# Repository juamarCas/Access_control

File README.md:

# Access Control
This project consist on a access control system. It uses microcontroller ESP8266 for internet connection, MQTT as my data transfer protocol, NodeJS as the backend programming Language, Express as the framework for the API and MySQL as the Database.</br>

The architecture of the complete project looks like this: </br>

# Dockerizing
be executed with containers, for this, there is the _docker-compose.yml_ file, just copy the content of app.env.example and paste it in a new file called app.env same to the db.env.example and broker.env.example, then fill the data needed in both files, build the two Dockerfile that are in DataBase and webApp and then run the docker-compose.</br>
In the docker-compose file describes that the image used for the app is nodeapp, so be sure when the image is builded is named as that, or change its name as your needs, same for the image of the database.

# Directory
In this section I discribe briefly what is each folder.</br>

## Access_Control
In this folder is the microcontroller project and schematics, is programmed using the PIO IDE.</br>

## DataBase
Thise folder contains the sql file for creating the tables needed.</br>

## HW_Design
This folder includes the KiCad project for the circuit.</br>

## Web-client
This folder includes the frontend of the projects, hasn't started yet this part.</br>

## webApp
This folder includes the NodeJS code for the backend.</br>

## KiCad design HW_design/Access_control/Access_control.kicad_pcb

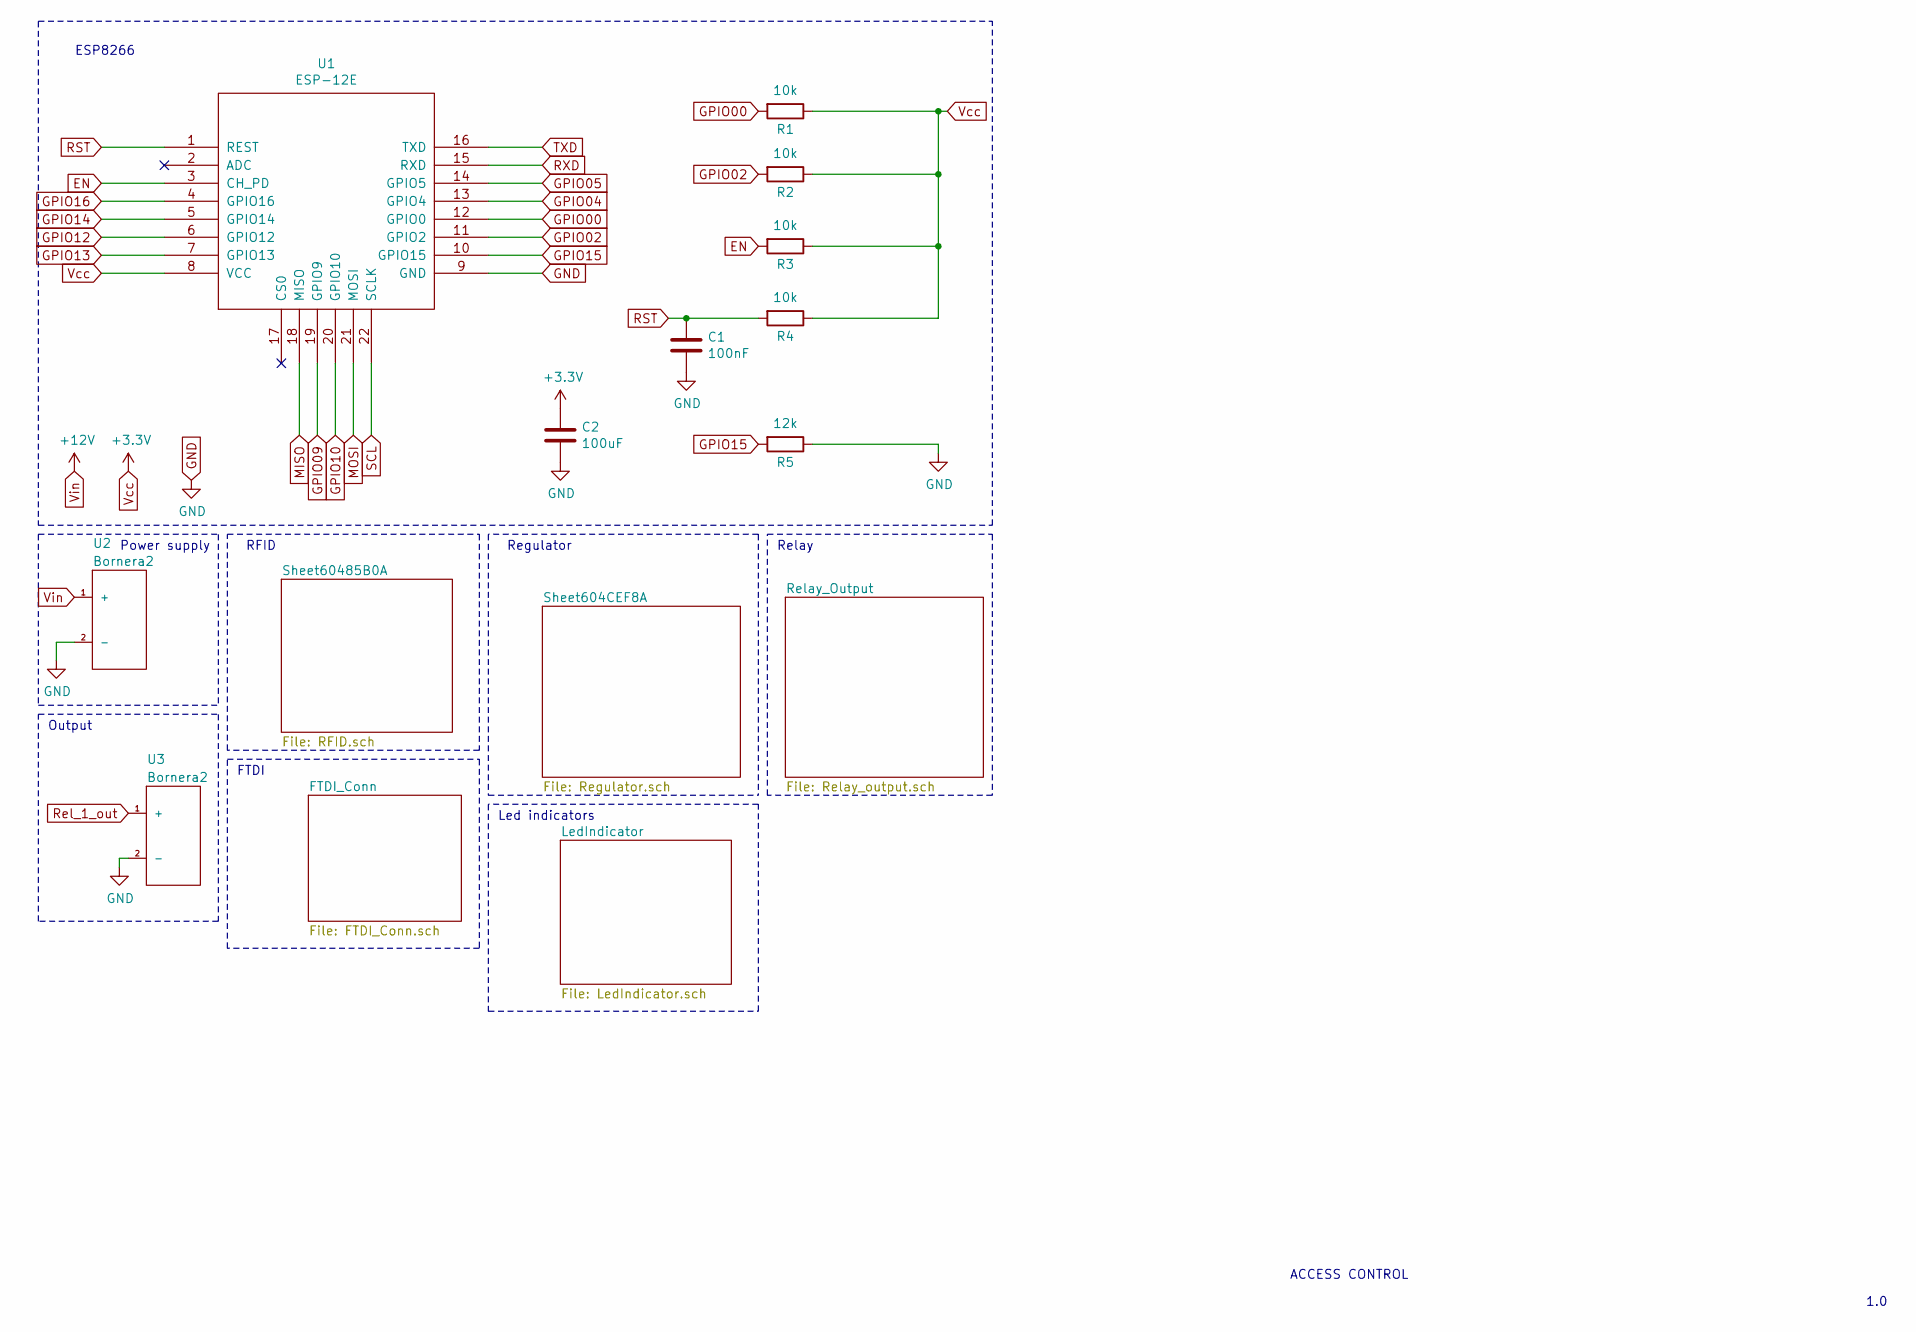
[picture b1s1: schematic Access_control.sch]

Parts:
C1: 100nF; C_1206_3216Metric
C2: 100uF; C_1206_3216Metric
R1, R2, R3, R4: 10k; R_0805_2012Metric
R5: 12k; R_0805_2012Metric
U1: ESP-12E; C_WiFiModule
U2, U3: Bornera2; Bronera_2

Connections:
EN: R3.2, U1.3 (CH_PD); also elsewhere on the board
GND: C1.2, C2.2, R5.1, U1.9 (GND), U2.2 (-), U3.2 (-); also elsewhere on the board
GPIO00: R1.2, U1.12 (GPIO0); also elsewhere on the board
GPIO02: R2.2, U1.11 (GPIO2); also elsewhere on the board
GPIO04: U1.13 (GPIO4)
GPIO05: U1.14 (GPIO5); also elsewhere on the board
GPIO09: U1.19 (GPIO9)
GPIO10: U1.20 (GPIO10)
GPIO12: U1.6 (GPIO12); also elsewhere on the board
GPIO13: U1.7 (GPIO13); also elsewhere on the board
GPIO14: U1.5 (GPIO14); also elsewhere on the board
GPIO15: R5.2, U1.10 (GPIO15); also elsewhere on the board
GPIO16: U1.4 (GPIO16); also elsewhere on the board
MISO: U1.18 (MISO)
MOSI: U1.21 (MOSI)
RST: C1.1, R4.2, U1.1 (REST)
RXD: U1.15 (RXD); also elsewhere on the board
Rel_1_out: U3.1 (+); also elsewhere on the board
SCL: U1.22 (SCLK)
TXD: U1.16 (TXD); also elsewhere on the board
Vcc: C2.1, R1.1, R2.1, R3.1, R4.1, U1.8 (VCC); also elsewhere on the board
Vin: U2.1 (+); also elsewhere on the board

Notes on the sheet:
ESP8266
RFID
Power supply
Regulator
ACCESS CONTROL
1.0
Relay
Output
FTDI
Led indicators

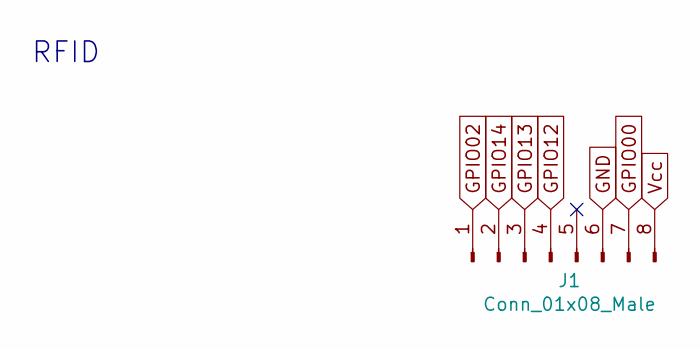
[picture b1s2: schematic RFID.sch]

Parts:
J1: Conn_01x08_Male; PinHeader_1x08_P2.54mm_Vertical

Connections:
GND: J1.6; also elsewhere on the board
GPIO00: J1.7; also elsewhere on the board
GPIO02: J1.1; also elsewhere on the board
GPIO12: J1.4; also elsewhere on the board
GPIO13: J1.3; also elsewhere on the board
GPIO14: J1.2; also elsewhere on the board
Vcc: J1.8; also elsewhere on the board

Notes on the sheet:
RFID

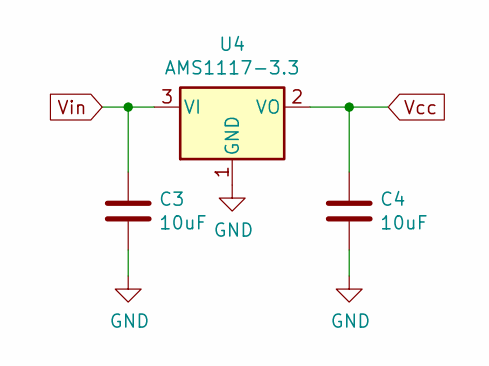
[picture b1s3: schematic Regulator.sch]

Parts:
C3, C4: 10uF; C_1206_3216Metric
U4: AMS1117-3.3; SOT-223-3_TabPin2

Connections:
GND: C3.2, C4.2, U4.1 (GND); also elsewhere on the board
Vcc: C4.1, U4.2 (VO); also elsewhere on the board
Vin: C3.1, U4.3 (VI); also elsewhere on the board

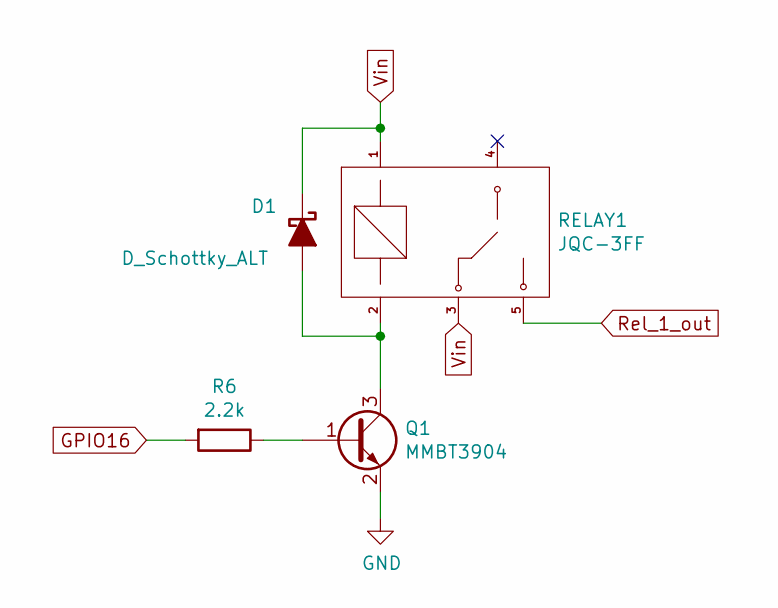
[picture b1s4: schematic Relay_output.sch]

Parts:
D1: D_Schottky_ALT; SMD_DIODE_4.6mmx2.90
Q1: MMBT3904; SOT-23
R6: 2.2k; R_0805_2012Metric
RELAY1: JQC-3FF; Relay

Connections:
GND: Q1.2 (E); also elsewhere on the board
GPIO16: R6.2; also elsewhere on the board
unnamed: D1.2 (A), Q1.3 (C), RELAY1.2
unnamed: Q1.1 (B), R6.1
Rel_1_out: RELAY1.5; also elsewhere on the board
Vin: D1.1 (K), RELAY1.1, RELAY1.3; also elsewhere on the board

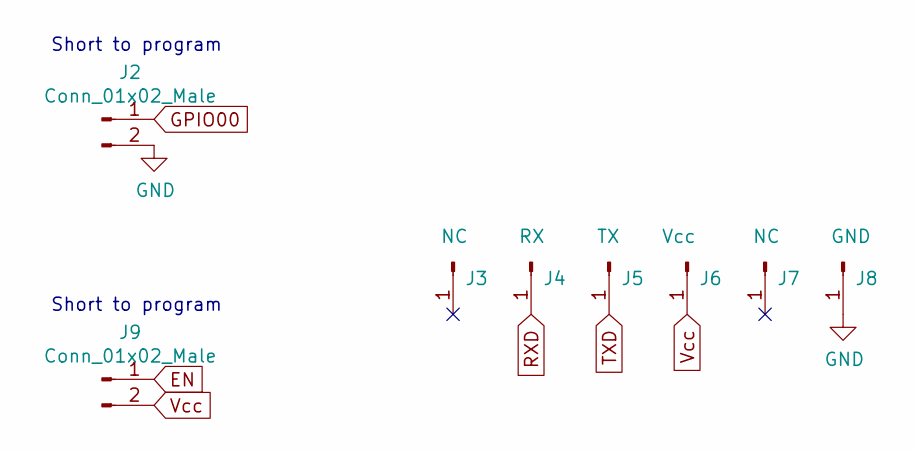
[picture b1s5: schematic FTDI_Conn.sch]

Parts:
J2, J9: Conn_01x02_Male; PinHeader_1x02_P2.54mm_Vertical
J3, J7: NC; PinHeader_1x01_P2.54mm_Vertical
J4: RX; PinHeader_1x01_P2.54mm_Vertical
J5: TX; PinHeader_1x01_P2.54mm_Vertical
J6: Vcc; PinHeader_1x01_P2.54mm_Vertical
J8: GND; PinHeader_1x01_P2.54mm_Vertical

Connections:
EN: J9.1; also elsewhere on the board
GND: J2.2, J8.1; also elsewhere on the board
GPIO00: J2.1; also elsewhere on the board
RXD: J4.1; also elsewhere on the board
TXD: J5.1; also elsewhere on the board
Vcc: J6.1, J9.2; also elsewhere on the board

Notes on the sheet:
Short to program

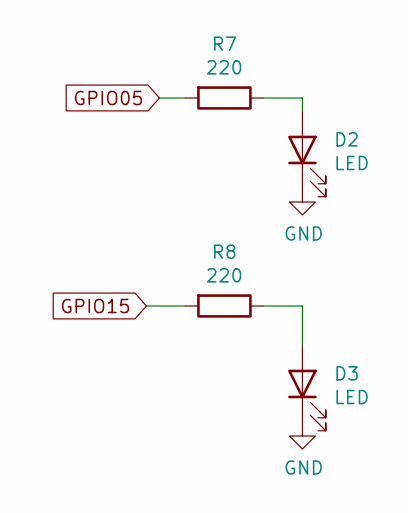
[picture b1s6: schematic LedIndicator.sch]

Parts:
D2, D3: LED; D_1206_3216Metric
R7, R8: 220; R_0805_2012Metric

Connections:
GND: D2.1 (K), D3.1 (K); also elsewhere on the board
GPIO05: R7.2; also elsewhere on the board
GPIO15: R8.2; also elsewhere on the board
unnamed: D2.2 (A), R7.1
unnamed: D3.2 (A), R8.1

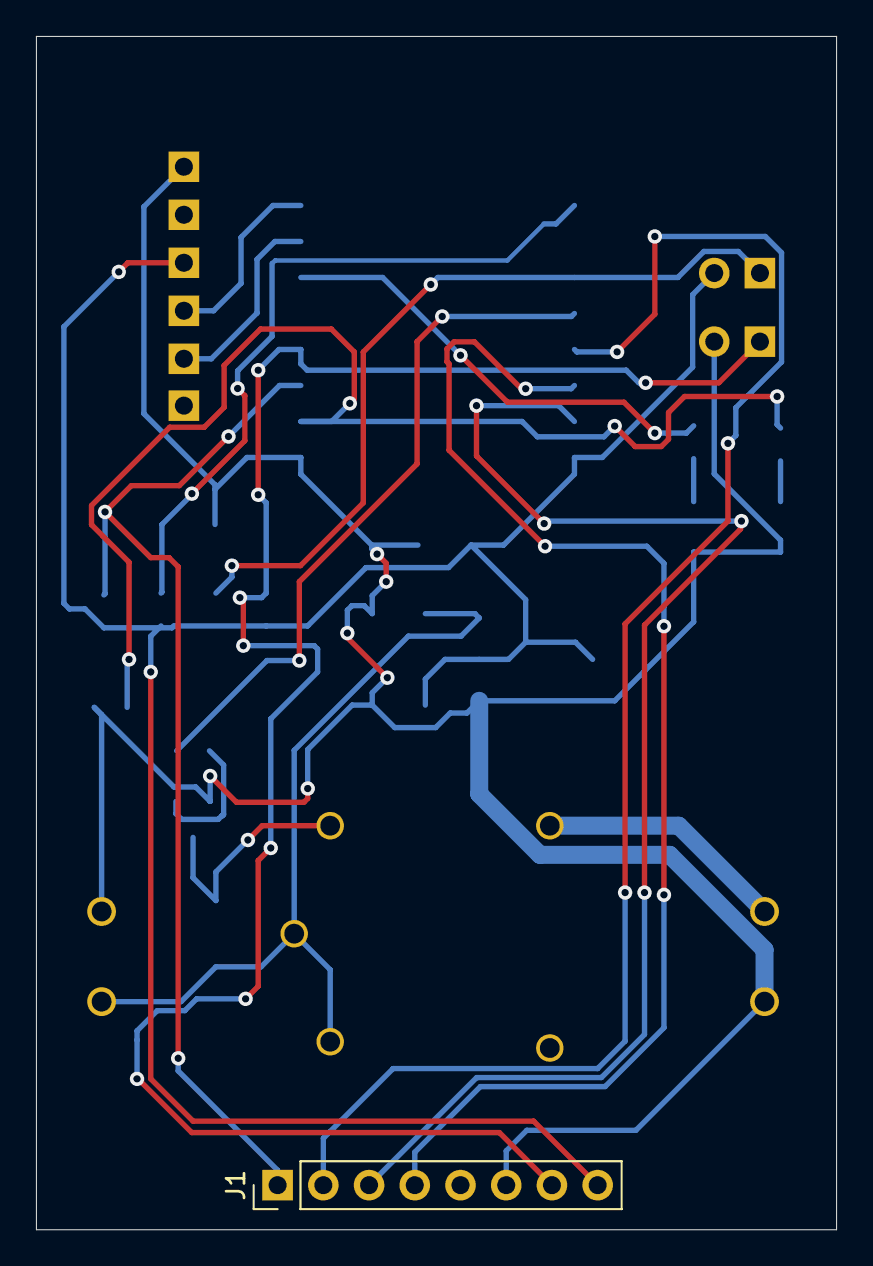
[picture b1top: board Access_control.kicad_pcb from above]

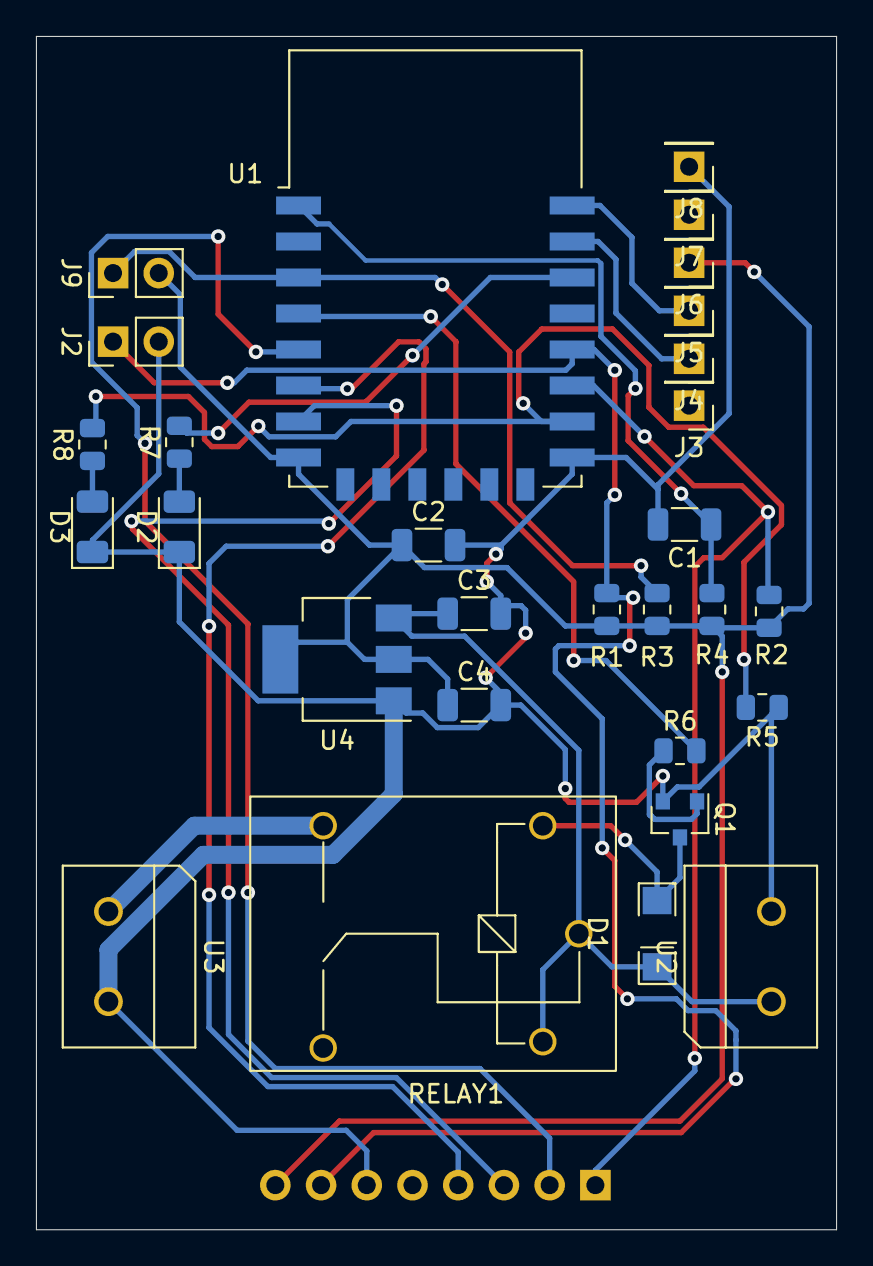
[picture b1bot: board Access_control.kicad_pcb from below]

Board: 2 copper layers, 44.4 x 66.3 mm, 30 parts (29 on the bottom side), 20 nets.

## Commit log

2021-02-12 added README
2021-02-12 Added MQTT connection to server
2021-02-12 implemented mysql auth to the broker
2021-02-12 added databse connection
2021-02-13 Database table implementation and access success/denied implemented
2021-02-14 deleted
2021-02-15 DB modified
2021-02-16 started creating the APIs
2021-02-24 Fixed posts to database
2021-02-24 changed queries
2021-02-24 Implemented singleton class for database
2021-02-26 DB class improved, added some routes
2021-02-26 added mqtt class
2021-03-04 Log API finished
2021-03-06 Schematic update
2021-03-07 pcb design
2021-03-07 fix pcb
2021-03-07 Fixed some table names
2021-03-07 Readme
2021-03-08 db readme
2021-03-08 fixed some response from the API
2021-03-08 Changed some pins configuration
2021-03-11 Dockerized
2021-03-13 Abstracted message event from mqtt
2021-03-14 Added JSON support microcontroller
2021-03-14 Added some comentaries
2021-03-14 added README to dockerignore
2021-03-14 dockerized emqx broker
2021-03-18 Updated database folder link
2021-03-18 building the images
2021-03-18 fixed env variables of broker
2021-03-18 fixed duplicated query column
2021-03-18 fixed column names
